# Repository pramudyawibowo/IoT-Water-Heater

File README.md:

## Project IoT : 
# Pemanas Air Otomatis dengan Monitoring Suhu dan Kelembapan Udara

## Anggota Kelompok 
| No |         Nama        |     NIM    |
|:--:|:-------------------:|:----------:|
|  1 | Abdur Rozak Junaidi | 1941720094 |
|  2 | Dwi Nur Oktaviani   | 1941720239 |
|  3 | Pramudya Wibowo     | 1941720054 |

## Pengkabelan

## Langkah Penggunaan Kode Program
* Atur pengkabelan seperti pada contoh diatas
* Ubah SSID dan Password dengan SSID dan Password dari Wifi yang digunakan.
* Atur alamat MQTT Broker yang digunakan.
* Atur pin-pin dari perangkat apabila diperlukan.
* Upload program, tunggu perangkat booting hingga LCD menunjukkan tampilan monitoring suhu.
* Akses node-red dashboard dengan alamat http://168.138.175.53:1880/ui
* Demo project dan uji coba dapat dilihat melalui link berikut https://youtu.be/ZZKoxPK8TpI

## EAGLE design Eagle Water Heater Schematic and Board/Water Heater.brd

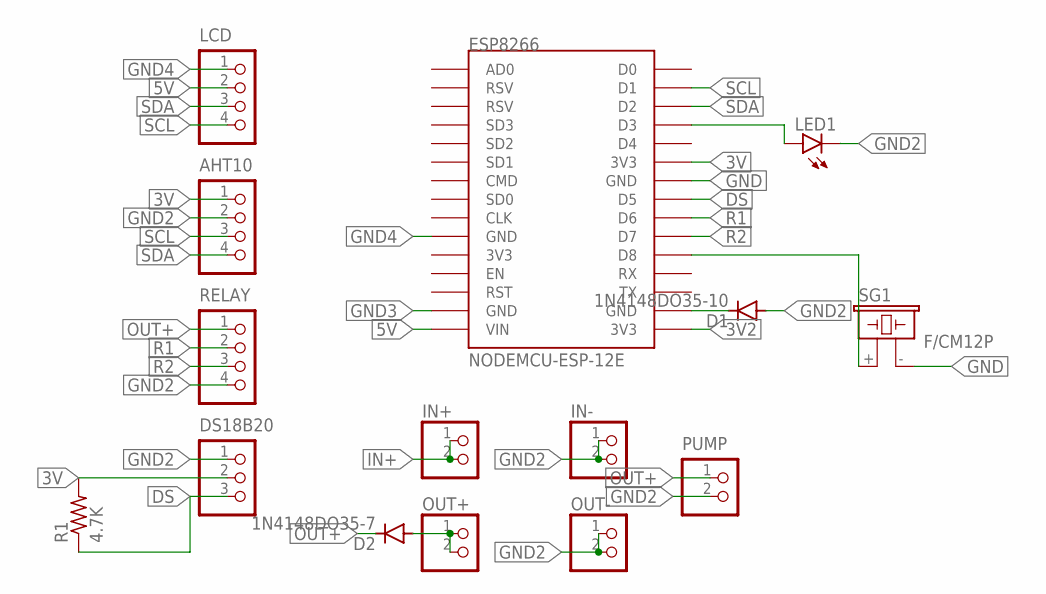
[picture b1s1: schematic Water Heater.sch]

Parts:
AHT10: B4B-XH-A
D1: 1N4148DO35-10; DO35-10
D2: 1N4148DO35-7; DO35-7
DS18B20: B3B-XH-A
ESP8266: NODEMCU-ESP-12E
IN+: PINHD-1X2; 1X02
IN-: PINHD-1X2; 1X02
LCD: B4B-XH-A
LED1: LED3MM
OUT+: PINHD-1X2; 1X02
OUT-: PINHD-1X2; 1X02
PUMP: B2B-XH-A
R1: 4.7K; 0204/7
RELAY: B4B-XH-A
SG1: F/CM12P

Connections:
3V: AHT10.1, DS18B20.2, ESP8266.3V3@1 (3V3), R1.2
3V2: ESP8266.3V3@2 (3V3)
5V: ESP8266.VIN, LCD.2
DS: DS18B20.3, ESP8266.D5, R1.1
GND: ESP8266.GND@2 (GND), SG1.- (2)
GND2: AHT10.2, D1.A, DS18B20.1, IN-.1, IN-.2, LED1.K (C), OUT-.1, OUT-.2, PUMP.2, RELAY.4
GND3: ESP8266.GND@1 (GND)
GND4: ESP8266.GND@0 (GND), LCD.1
IN+: IN+.1, IN+.2
unnamed: ESP8266.D3, LED1.A
unnamed: ESP8266.D8, SG1.+ (1)
unnamed: D1.C, ESP8266.GND@3 (GND)
unnamed: D2.A, OUT+.1, OUT+.2
OUT+: D2.C, PUMP.1, RELAY.1
R1: ESP8266.D6, RELAY.2
R2: ESP8266.D7, RELAY.3
SCL: AHT10.3, ESP8266.D1, LCD.4
SDA: AHT10.4, ESP8266.D2, LCD.3

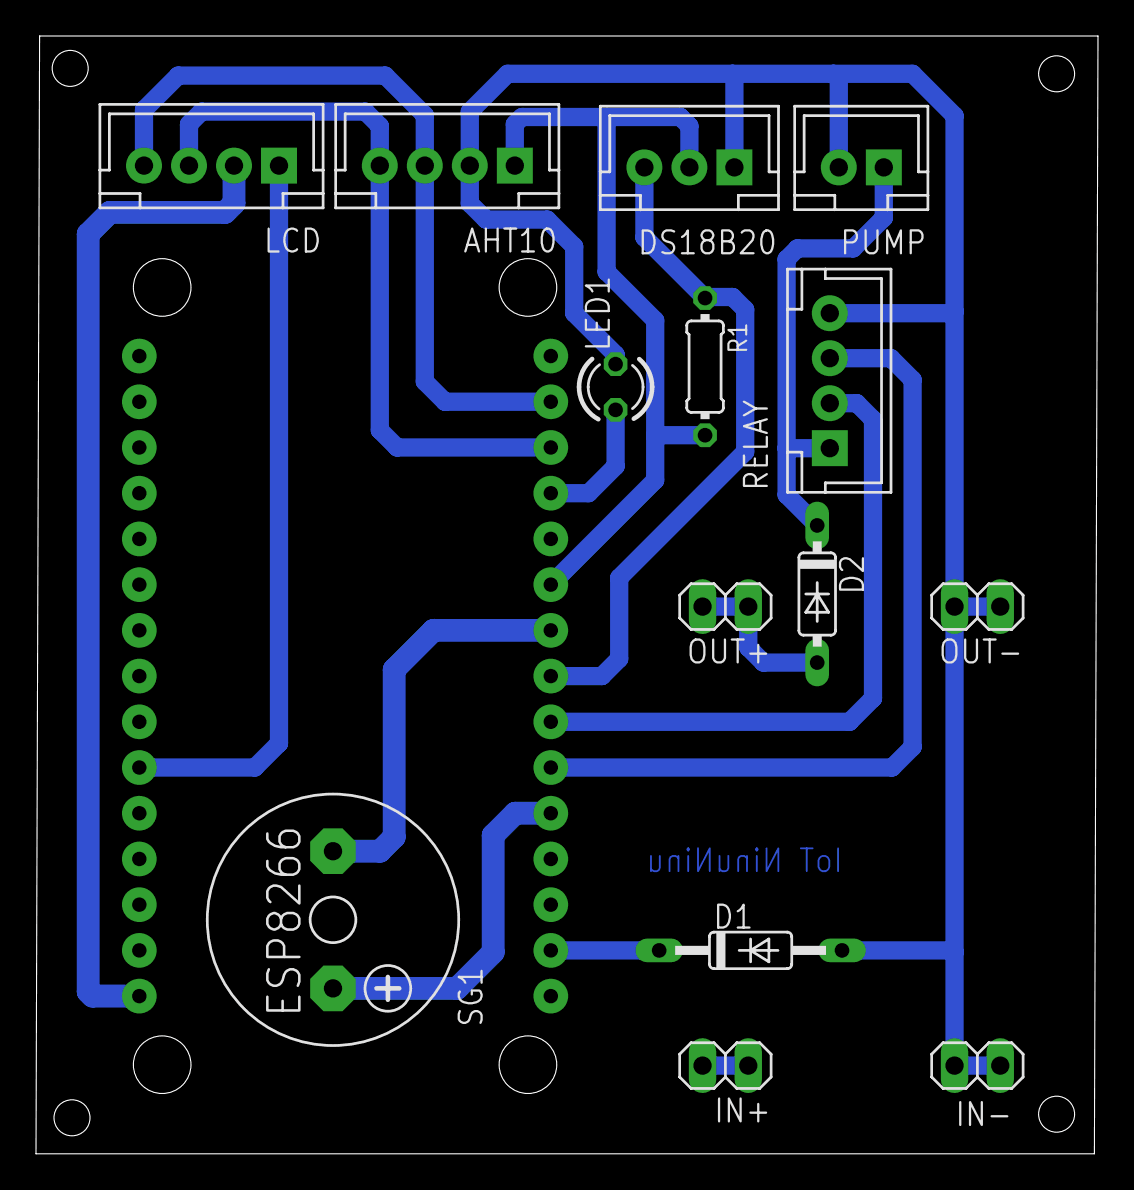
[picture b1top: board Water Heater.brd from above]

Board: 2 copper layers, 59.0 x 62.1 mm, 15 parts (0 on the bottom side), 16 nets.

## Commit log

2022-06-22 Project IoT
2022-06-22 Menambahkan pengkabelan fritzing
2022-06-22 Menambahkan skematik dan board eagle untuk pcb
2022-06-23 Change MQTT Broker Server IP Address
2022-06-23 Change Node Red Dashboard Address
2024-05-20 [ImgBot] Optimize images
    /Fritzing/Wiring.jpg -- 567.66kb -> 470.50kb (17.12%)
